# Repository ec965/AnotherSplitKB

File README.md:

# GIS
GIS is a recursive acronym that stands for "GIS is split"

* Choc switches
* reversible split PCB
* OLED
* Pro micro

## Firmware
[QMK](https://github.com/ec965/qmk_firmware/tree/split-kb/keyboards/gis)

## Spec

* 58 switches

## Pictures

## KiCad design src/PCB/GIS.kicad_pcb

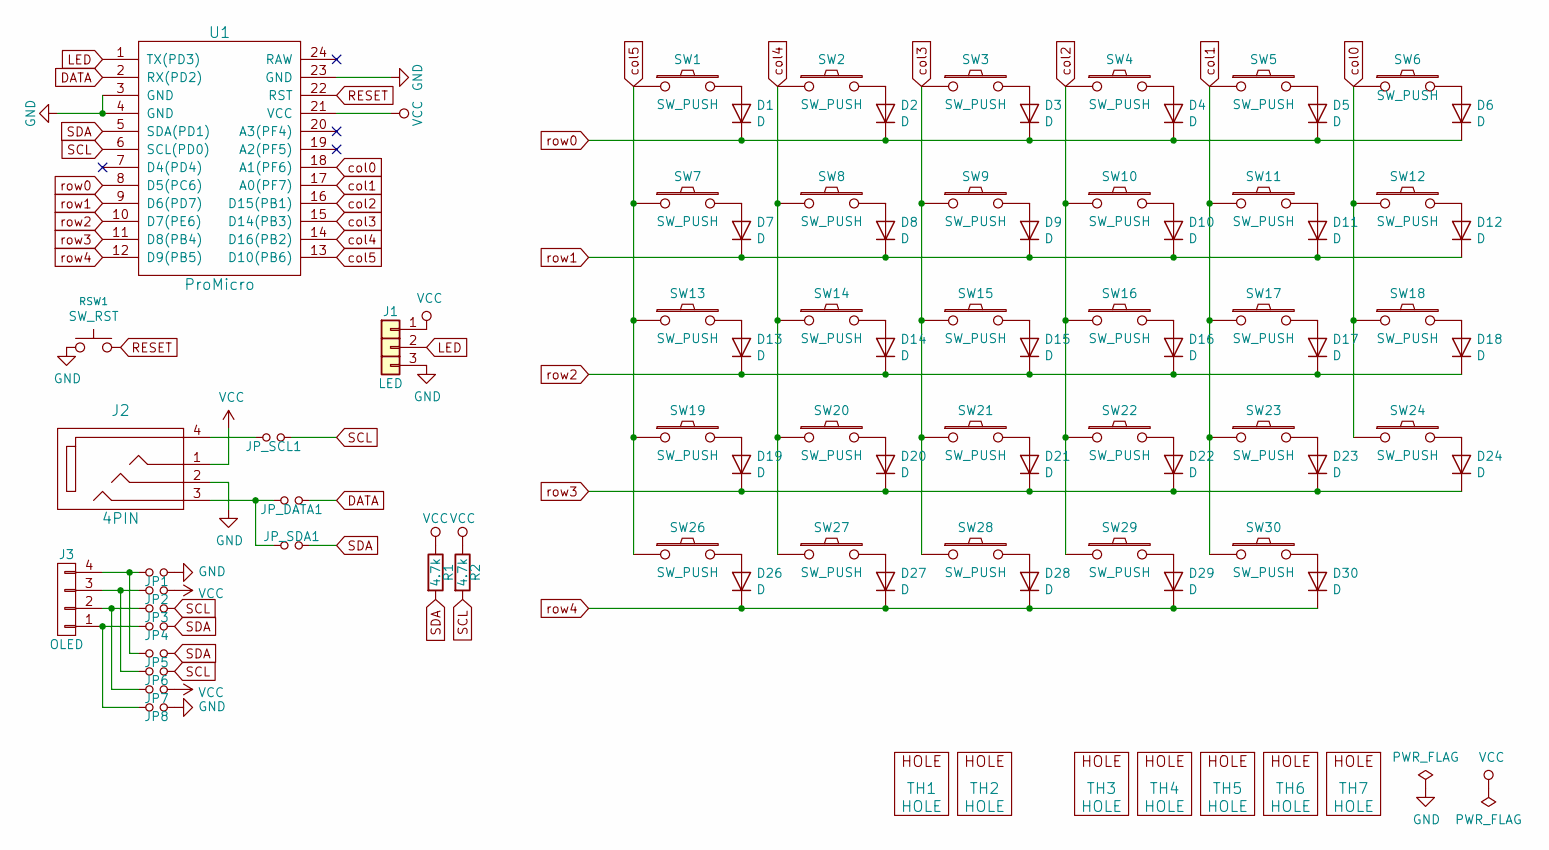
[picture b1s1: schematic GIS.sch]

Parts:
D1, D2, D3, D4, D5, D6, D7, D8, D9, D10, D11, D12, D13, D14, D15, D16, D17, D18, D19, D20, D21, D22, D23, D24, D26, D27, D28, D29, D30: D; D3_TH_SMD_v2
J1: LED
J2: 4PIN; MJ-4PP-9
J3: OLED; OLED_4Pin
JP1, JP2, JP3, JP4, JP5, JP6, JP7, JP8: Jumper_NO_Small; Jumper
JP_DATA1: Jumper_NO_Small; Jumper
JP_SCL1: Jumper_NO_Small; Jumper
JP_SDA1: Jumper_NO_Small; Jumper
R1, R2: 4.7k; R_0603_1608Metric_Pad0.98x0.95mm_HandSolder
RSW1: SW_RST; TACT_SWITCH_TVBP06
SW1, SW2, SW3, SW4, SW5, SW6, SW7, SW8, SW9, SW10, SW11, SW12, SW13, SW14, SW15, SW16, SW17, SW18, SW19, SW20, SW21, SW22, SW23, SW24, SW26, SW27, SW28, SW29, SW30: SW_PUSH; Kailh-PG1350-1u-reversible-flip
TH1, TH2: HOLE; M2_HOLE_PCB
TH3, TH4, TH5, TH6, TH7: HOLE; MountingHole_2.2mm_M2_Pad_Via
U1: ProMicro

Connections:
DATA: JP_DATA1.2, U1.2 (RX(PD2))
GND: J1.3, J2.2, JP1.2, JP8.2, RSW1.1, U1.3 (GND), U1.4 (GND), U1.23 (GND)
LED: J1.2, U1.1 (TX(PD3))
unnamed: D1.2 (A), SW1.2
unnamed: D2.2 (A), SW2.2
unnamed: D3.2 (A), SW3.2
unnamed: D4.2 (A), SW4.2
unnamed: D5.2 (A), SW5.2
unnamed: D6.2 (A), SW6.2
unnamed: D7.2 (A), SW7.2
unnamed: D8.2 (A), SW8.2
unnamed: D9.2 (A), SW9.2
unnamed: D10.2 (A), SW10.2
unnamed: D11.2 (A), SW11.2
unnamed: D12.2 (A), SW12.2
unnamed: D13.2 (A), SW13.2
unnamed: D14.2 (A), SW14.2
unnamed: D15.2 (A), SW15.2
unnamed: D16.2 (A), SW16.2
unnamed: D17.2 (A), SW17.2
unnamed: D18.2 (A), SW18.2
unnamed: D19.2 (A), SW19.2
unnamed: D20.2 (A), SW20.2
unnamed: D21.2 (A), SW21.2
unnamed: D22.2 (A), SW22.2
unnamed: D23.2 (A), SW23.2
unnamed: D24.2 (A), SW24.2
unnamed: D26.2 (A), SW26.2
unnamed: D27.2 (A), SW27.2
unnamed: D28.2 (A), SW28.2
unnamed: D29.2 (A), SW29.2
unnamed: D30.2 (A), SW30.2
unnamed: J2.3, JP_DATA1.1, JP_SDA1.2
unnamed: J2.4, JP_SCL1.1
unnamed: J3.1, JP4.1, JP8.1
unnamed: J3.2, JP3.1, JP7.1
unnamed: J3.3, JP2.1, JP6.1
unnamed: J3.4, JP1.1, JP5.1
RESET: RSW1.2, U1.22 (RST)
SCL: JP3.2, JP6.2, JP_SCL1.2, R2.2, U1.6 (SCL(PD0))
SDA: JP4.2, JP5.2, JP_SDA1.1, R1.2, U1.5 (SDA(PD1))
VCC: J1.1, J2.1, JP2.2, JP7.2, R1.1, R2.1, U1.21 (VCC)
col0: SW6.1, SW12.1, SW18.1, SW24.1, U1.18 (A1(PF6))
col1: SW5.1, SW11.1, SW17.1, SW23.1, SW30.1, U1.17 (A0(PF7))
col2: SW4.1, SW10.1, SW16.1, SW22.1, SW29.1, U1.16 (D15(PB1))
col3: SW3.1, SW9.1, SW15.1, SW21.1, SW28.1, U1.15 (D14(PB3))
col4: SW2.1, SW8.1, SW14.1, SW20.1, SW27.1, U1.14 (D16(PB2))
col5: SW1.1, SW7.1, SW13.1, SW19.1, SW26.1, U1.13 (D10(PB6))
row0: D1.1 (K), D2.1 (K), D3.1 (K), D4.1 (K), D5.1 (K), D6.1 (K), U1.8 (D5(PC6))
row1: D7.1 (K), D8.1 (K), D9.1 (K), D10.1 (K), D11.1 (K), D12.1 (K), U1.9 (D6(PD7))
row2: D13.1 (K), D14.1 (K), D15.1 (K), D16.1 (K), D17.1 (K), D18.1 (K), U1.10 (D7(PE6))
row3: D19.1 (K), D20.1 (K), D21.1 (K), D22.1 (K), D23.1 (K), D24.1 (K), U1.11 (D8(PB4))
row4: D26.1 (K), D27.1 (K), D28.1 (K), D29.1 (K), D30.1 (K), U1.12 (D9(PB5))

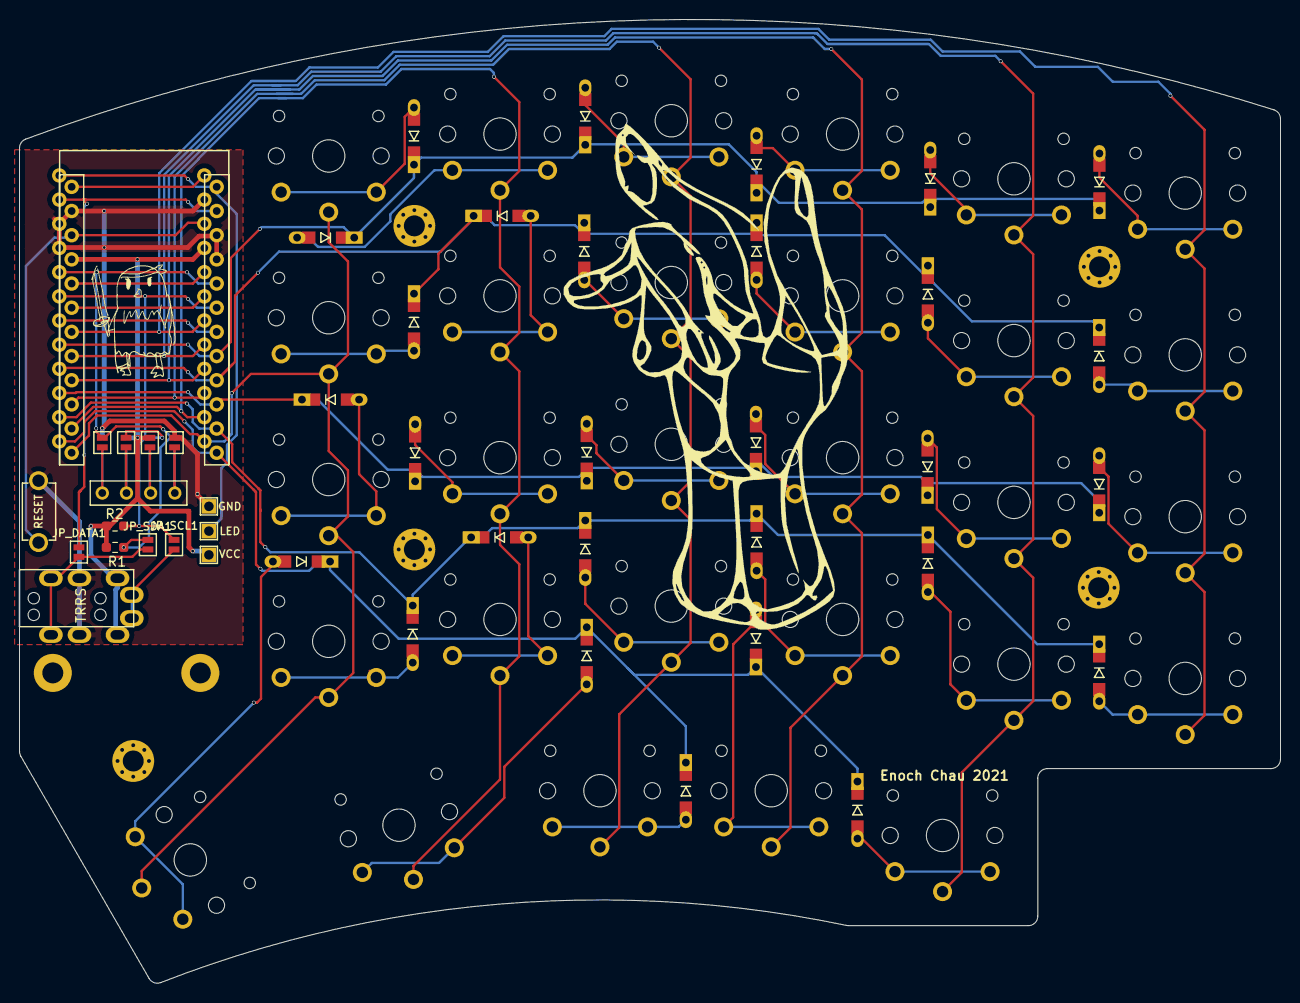
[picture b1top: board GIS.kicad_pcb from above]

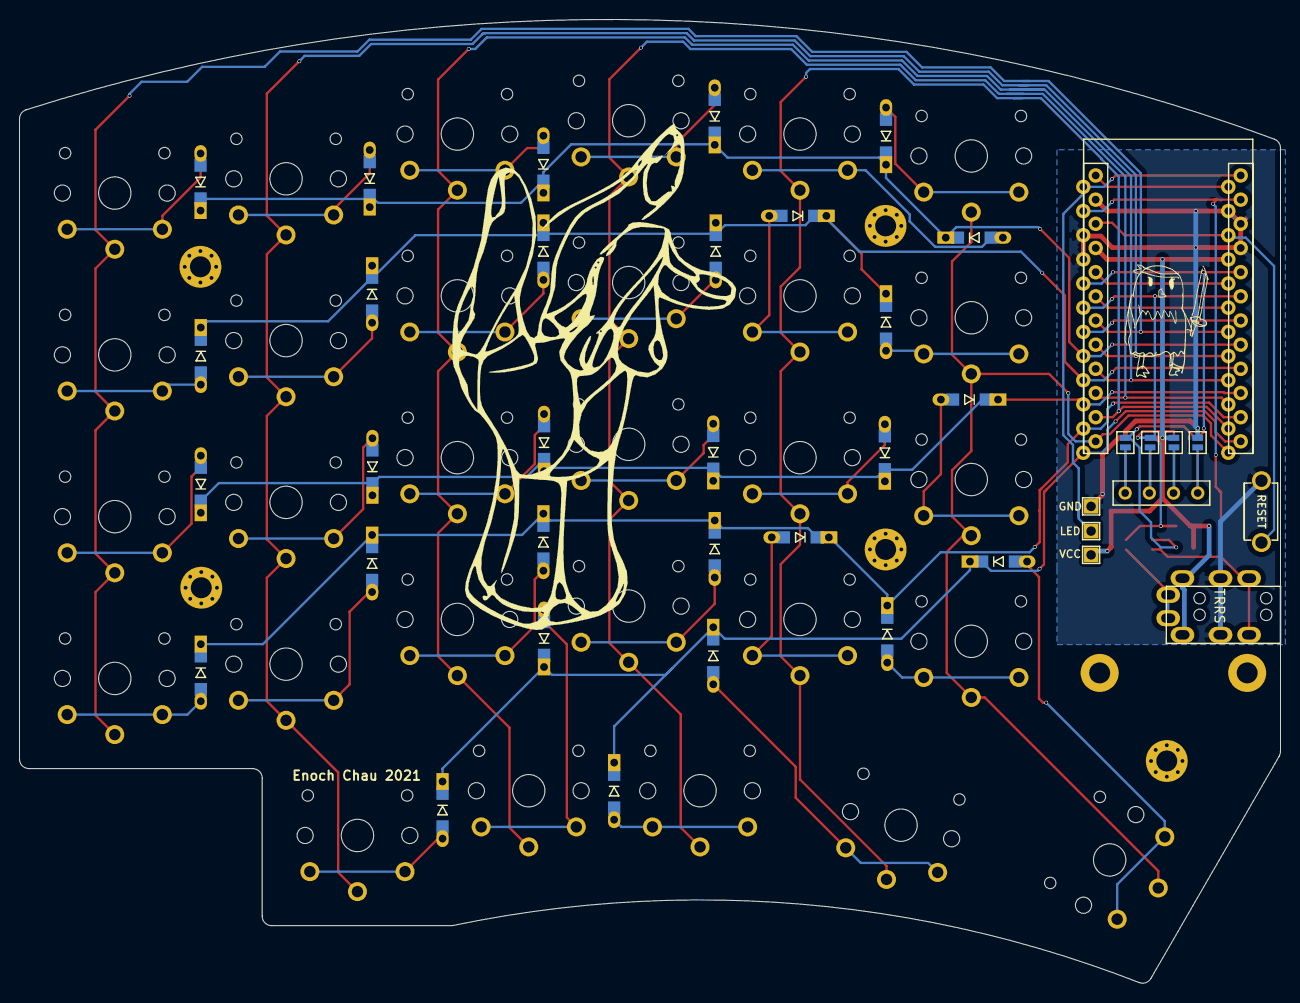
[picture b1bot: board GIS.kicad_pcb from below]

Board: 2 copper layers, 132.5 x 101.3 mm, 83 parts (4 on the bottom side), 53 nets.

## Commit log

2021-04-10 init
2021-04-10 adding art
2021-04-10 fixing spacing for 1.5u keycap
2021-05-01 adding silks and finalizing design
2021-05-01 renaming
2021-05-02 fixing diode hole size
2021-05-02 starting to fix pcb shape flaw
2021-05-03 switching to better dual diode footprint
2021-05-03 adding pictures
2021-05-03 updating license
2021-07-08 adding built pic
2021-07-08 rotate pic
